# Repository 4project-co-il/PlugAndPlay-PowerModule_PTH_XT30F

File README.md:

# PlugAndPlay: Power Module with XT30 Female connector
This is the repository with the files for Power Module for the PlugAndPlay boards.

That module is equiped with XT30 female connector that is rated for up to 30A of current.
The PCB and connections of the power modules on PlugAndPlay devices are designed to pass up to 10A, although wasn't tested.

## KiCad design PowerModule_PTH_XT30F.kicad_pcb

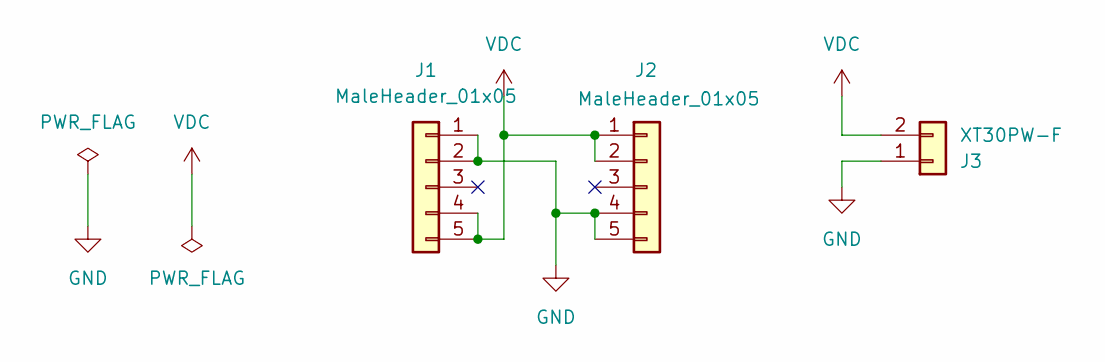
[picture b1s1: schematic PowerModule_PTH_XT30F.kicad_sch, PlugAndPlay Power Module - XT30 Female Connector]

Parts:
J1: MaleHeader_01x05; PinSocket_1x05_P2.54mm_Vertical_SMD_Pin1Right; MPN RealRun
J2: MaleHeader_01x05; PinSocket_1x05_P2.54mm_Vertical_SMD_Pin1Left; MPN RealRun
J3: XT30PW-F; AMASS_XT30PW-F_1x02_P2.50mm_Horizontal

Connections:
GND: J1.1, J1.2, J2.4, J2.5, J3.1
VDC: J1.4, J1.5, J2.1, J2.2, J3.2

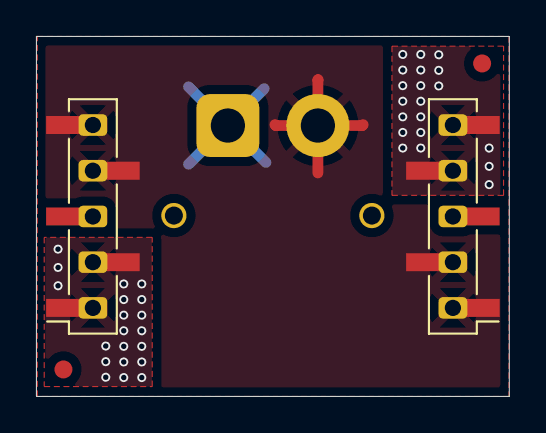
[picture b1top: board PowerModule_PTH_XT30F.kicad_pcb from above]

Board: 2 copper layers, 26.3 x 20.0 mm, 3 parts (1 on the bottom side), 2 nets.
